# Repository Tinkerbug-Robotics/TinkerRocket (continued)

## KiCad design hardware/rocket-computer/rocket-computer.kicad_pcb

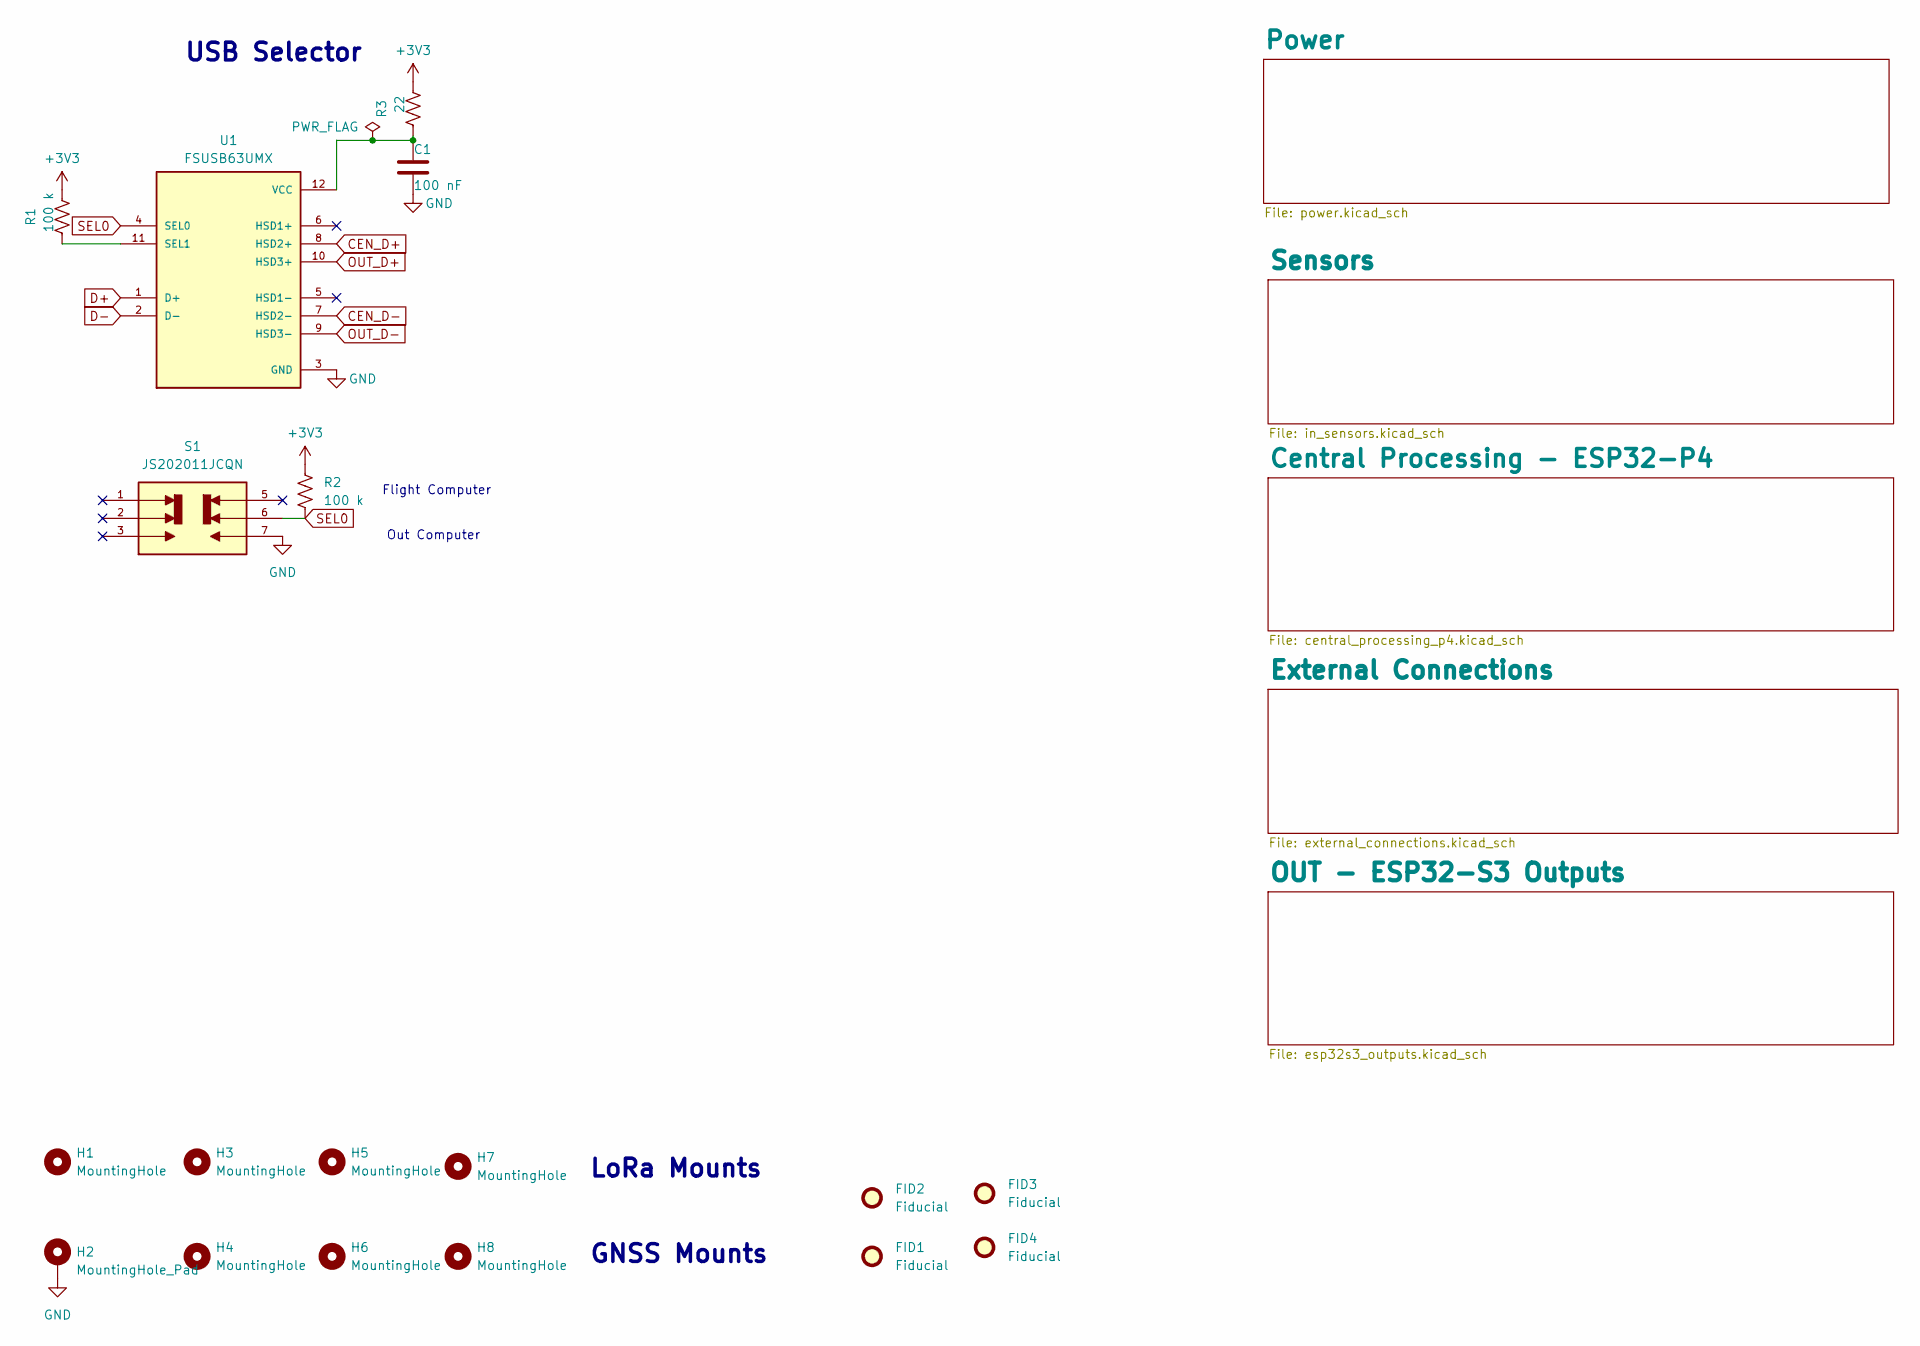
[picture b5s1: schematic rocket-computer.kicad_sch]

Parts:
C1: 100 nF; C_0402_1005Metric; MPN CL05B104KO5NNNC
FID1, FID2, FID3, FID4: Fiducial; Fiducial_0.5mm_Mask1mm
H1, H3, H4, H5, H6, H7, H8: MountingHole; MountingHole_2.2mm_M2_DIN965_Pad_TopBottom
H2: MountingHole_Pad; MountingHole_2.2mm_M2_DIN965_Pad_TopBottom
R1, R2: 100 k; R_0402_1005Metric; MPN RC0402FR-07100KL
R3: 22; R_0402_1005Metric; MPN RC0402FR-0722RL
S1: JS202011JCQN; SW_JS202011JCQN; PARTREV 11 Nov 19; DigiKey_Part_Number CKN10723CT-ND
U1: FSUSB63UMX; QFN40P180X180X55-12N; MPN FSUSB63UMX

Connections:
+3V3: R1.2, R2.2, R3.2; also elsewhere on the board
CEN_D+: U1.8 (HSD2+); also elsewhere on the board
CEN_D-: U1.7 (HSD2-); also elsewhere on the board
D+: U1.1 (D+); also elsewhere on the board
D-: U1.2 (D-); also elsewhere on the board
GND: C1.2, H2.1 (1_1), S1.7, U1.3 (GND); also elsewhere on the board
unnamed: R1.1, U1.11 (SEL1)
unnamed: C1.1, R3.1, U1.12 (VCC)
OUT_D+: U1.10 (HSD3+); also elsewhere on the board
OUT_D-: U1.9 (HSD3-); also elsewhere on the board
SEL0: R2.1, S1.6, U1.4 (SEL0)

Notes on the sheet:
GNSS Mounts
Out Computer
USB Selector
Flight Computer
LoRa Mounts

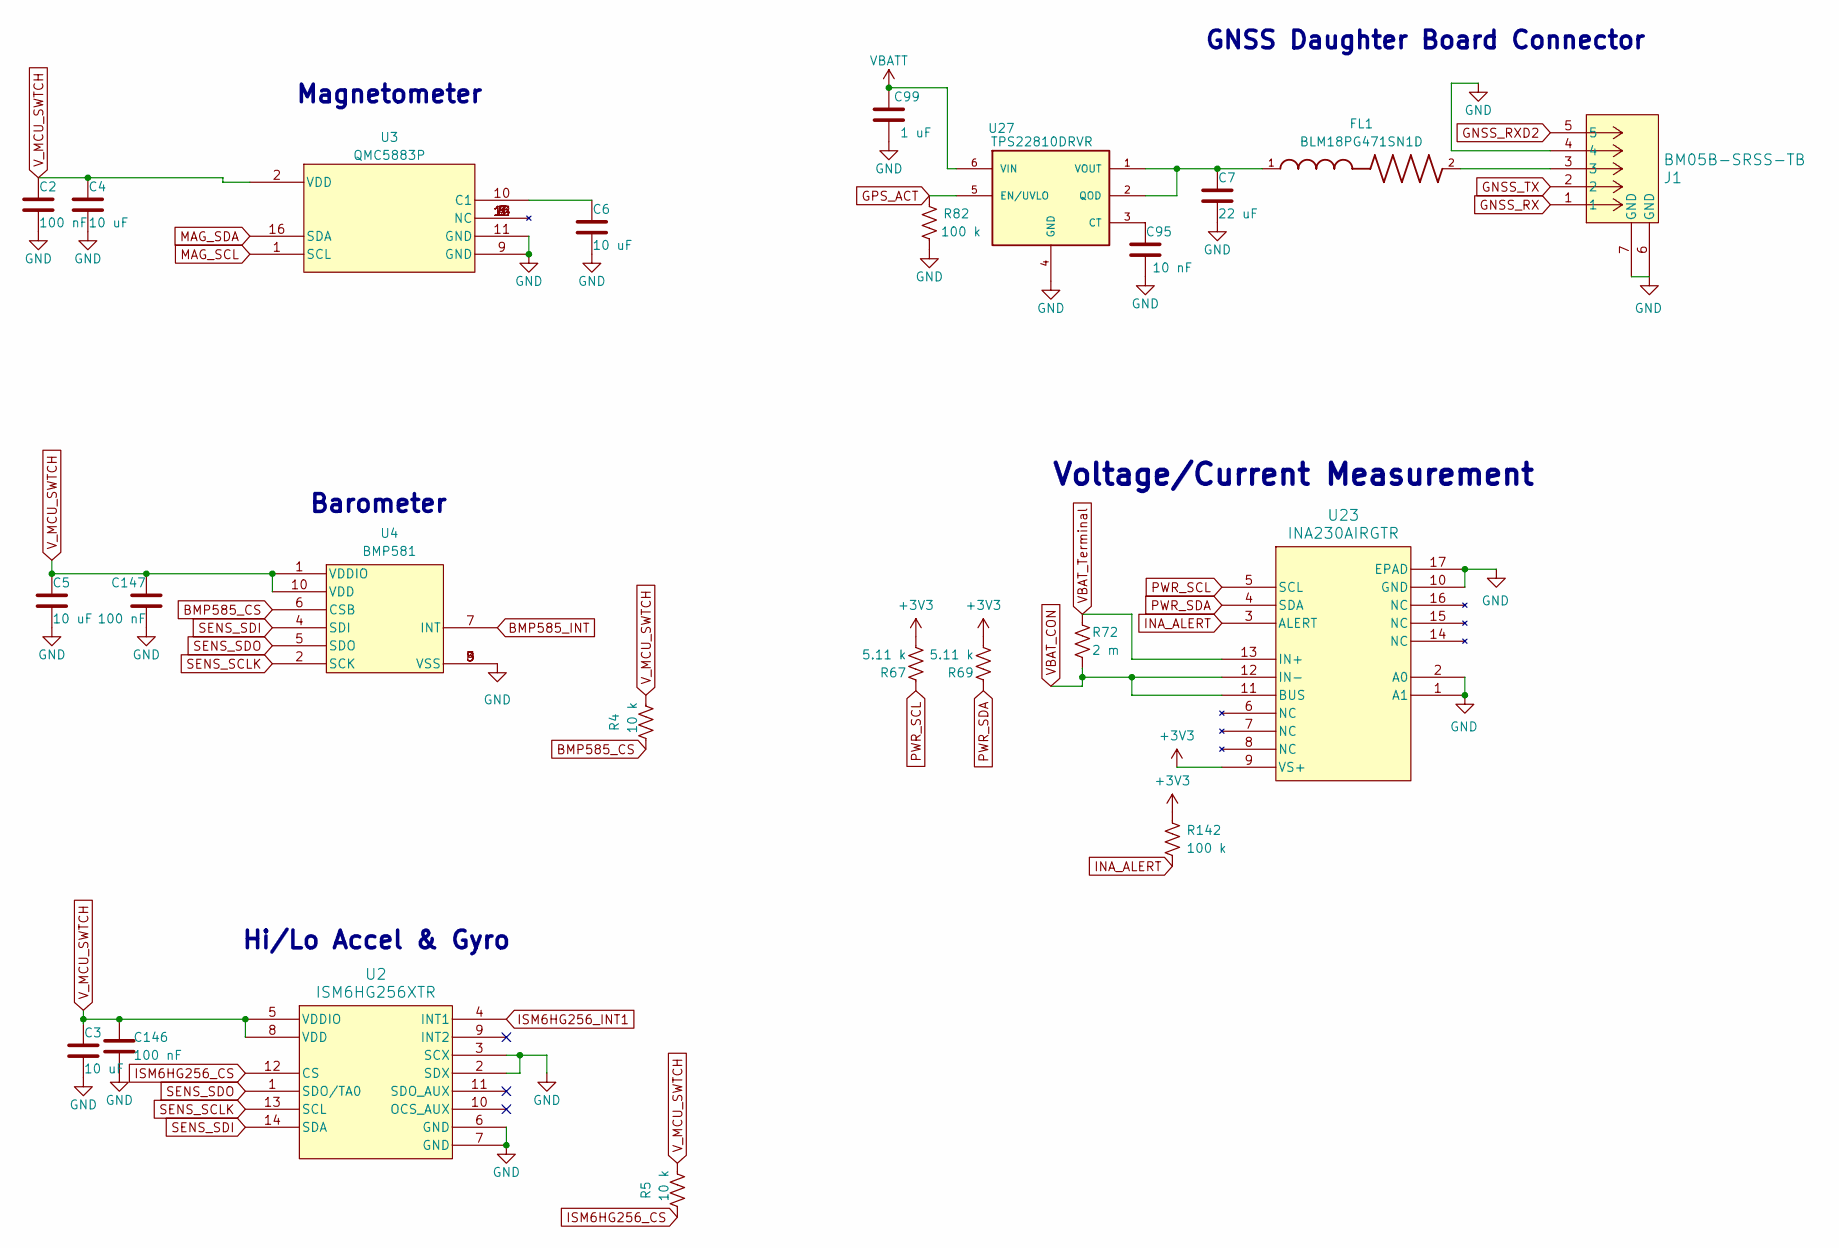
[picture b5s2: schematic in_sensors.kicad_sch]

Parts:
C2, C146, C147: 100 nF; C_0402_1005Metric; MPN CL05B104KO5NNNC
C3, C4, C5, C6: 10 uF; C_0402_1005Metric; MPN CL05A106MQ5NUNC
C7: 22 uF; C_0805_2012Metric; MPN CL21A226MOQNNNE
C95: 10 nF; C_0402_1005Metric; MPN CL05B103KB5NNNC
C99: 1 uF; C_0402_1005Metric; MPN CL05A105KO5NNNC
FL1: BLM18PG471SN1D; BEADC1608X95N; MPN BLM18PG471SN1D
J1: BM05B-SRSS-TB; CONN_BM05B-SRSS-TB_JST; MPN BM05B-SRSS-TB
R4, R5: 10 k; R_0402_1005Metric; MPN RC0402FR-0710KL
R67, R69: 5.11 k; R_0402_1005Metric; MPN RC0402FR-075K11L
R72: 2 m; R_0805_2012Metric; MPN PA0805FRF870R002L
R82, R142: 100 k; R_0402_1005Metric; MPN RC0402FR-07100KL
U2: ISM6HG256XTR; U_LGA-14L_2p5X3p0X0p83_STM; MPN ISM6HG256XTR
U3: QMC5883P; QMC5883P_LGA-16_3x3; MPN QMC5883P
U4: BMP581; BMP581_LGA-10_2x2; MPN BMP581
U23: INA230AIRGTR; RGT16_1P7X1P7; MPN INA230AIRGTR
U27: TPS22810DRVR; SON65P200X200X80-7N; MPN TPS22810DRVR

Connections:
+3V3: R67.1, R69.1, R142.1, U23.9 (VS+); also elsewhere on the board
BMP585_CS: R4.1, U4.6 (CSB); also elsewhere on the board
BMP585_INT: U4.7 (INT); also elsewhere on the board
GND: C2.2, C3.2, C4.2, C5.2, C6.2, C7.2, C95.2, C99.2, C146.2, C147.2, J1.4, J1.6 (GND), J1.7 (GND), R82.2, U2.2 (SDX), U2.3 (SCX), U2.6 (GND), U2.7 (GND), U3.9 (GND), U3.11 (GND), U4.3 (VSS), U4.8 (VSS), U4.9 (VSS), U23.1 (A1), U23.2 (A0), U23.10 (GND), U23.17 (EPAD), U27.4 (GND), U27.7 (GND); also elsewhere on the board
GNSS_RX: J1.1; also elsewhere on the board
GNSS_RXD2: J1.5; also elsewhere on the board
GNSS_TX: J1.2; also elsewhere on the board
GPS_ACT: R82.1, U27.5 (EN/UVLO); also elsewhere on the board
INA_ALERT: R142.2, U23.3 (ALERT); also elsewhere on the board
ISM6HG256_CS: R5.1, U2.12 (CS); also elsewhere on the board
ISM6HG256_INT1: U2.4 (INT1); also elsewhere on the board
MAG_SCL: U3.1 (SCL); also elsewhere on the board
MAG_SDA: U3.16 (SDA); also elsewhere on the board
unnamed: FL1.2, J1.3
unnamed: C6.1, U3.10 (C1)
unnamed: C95.1, U27.3 (CT)
unnamed: C7.1, FL1.1, U27.1 (VOUT), U27.2 (QOD)
PWR_SCL: R67.2, U23.5 (SCL); also elsewhere on the board
PWR_SDA: R69.2, U23.4 (SDA); also elsewhere on the board
SENS_SCLK: U2.13 (SCL), U4.2 (SCK); also elsewhere on the board
SENS_SDI: U2.14 (SDA), U4.4 (SDI); also elsewhere on the board
SENS_SDO: U2.1 (SDO/TA0), U4.5 (SDO); also elsewhere on the board
VBATT: C99.1, U27.6 (VIN); also elsewhere on the board
VBAT_CON: R72.1, U23.11 (BUS), U23.12 (IN-); also elsewhere on the board
VBAT_Terminal: R72.2, U23.13 (IN+); also elsewhere on the board
V_MCU_SWTCH: C2.1, C3.1, C4.1, C5.1, C146.1, C147.1, R4.2, R5.2, U2.5 (VDDIO), U2.8 (VDD), U3.2 (VDD), U4.1 (VDDIO), U4.10 (VDD); also elsewhere on the board

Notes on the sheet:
Barometer
Hi/Lo Accel & Gyro
Magnetometer
GNSS Daughter Board Connector
Voltage/Current Measurement

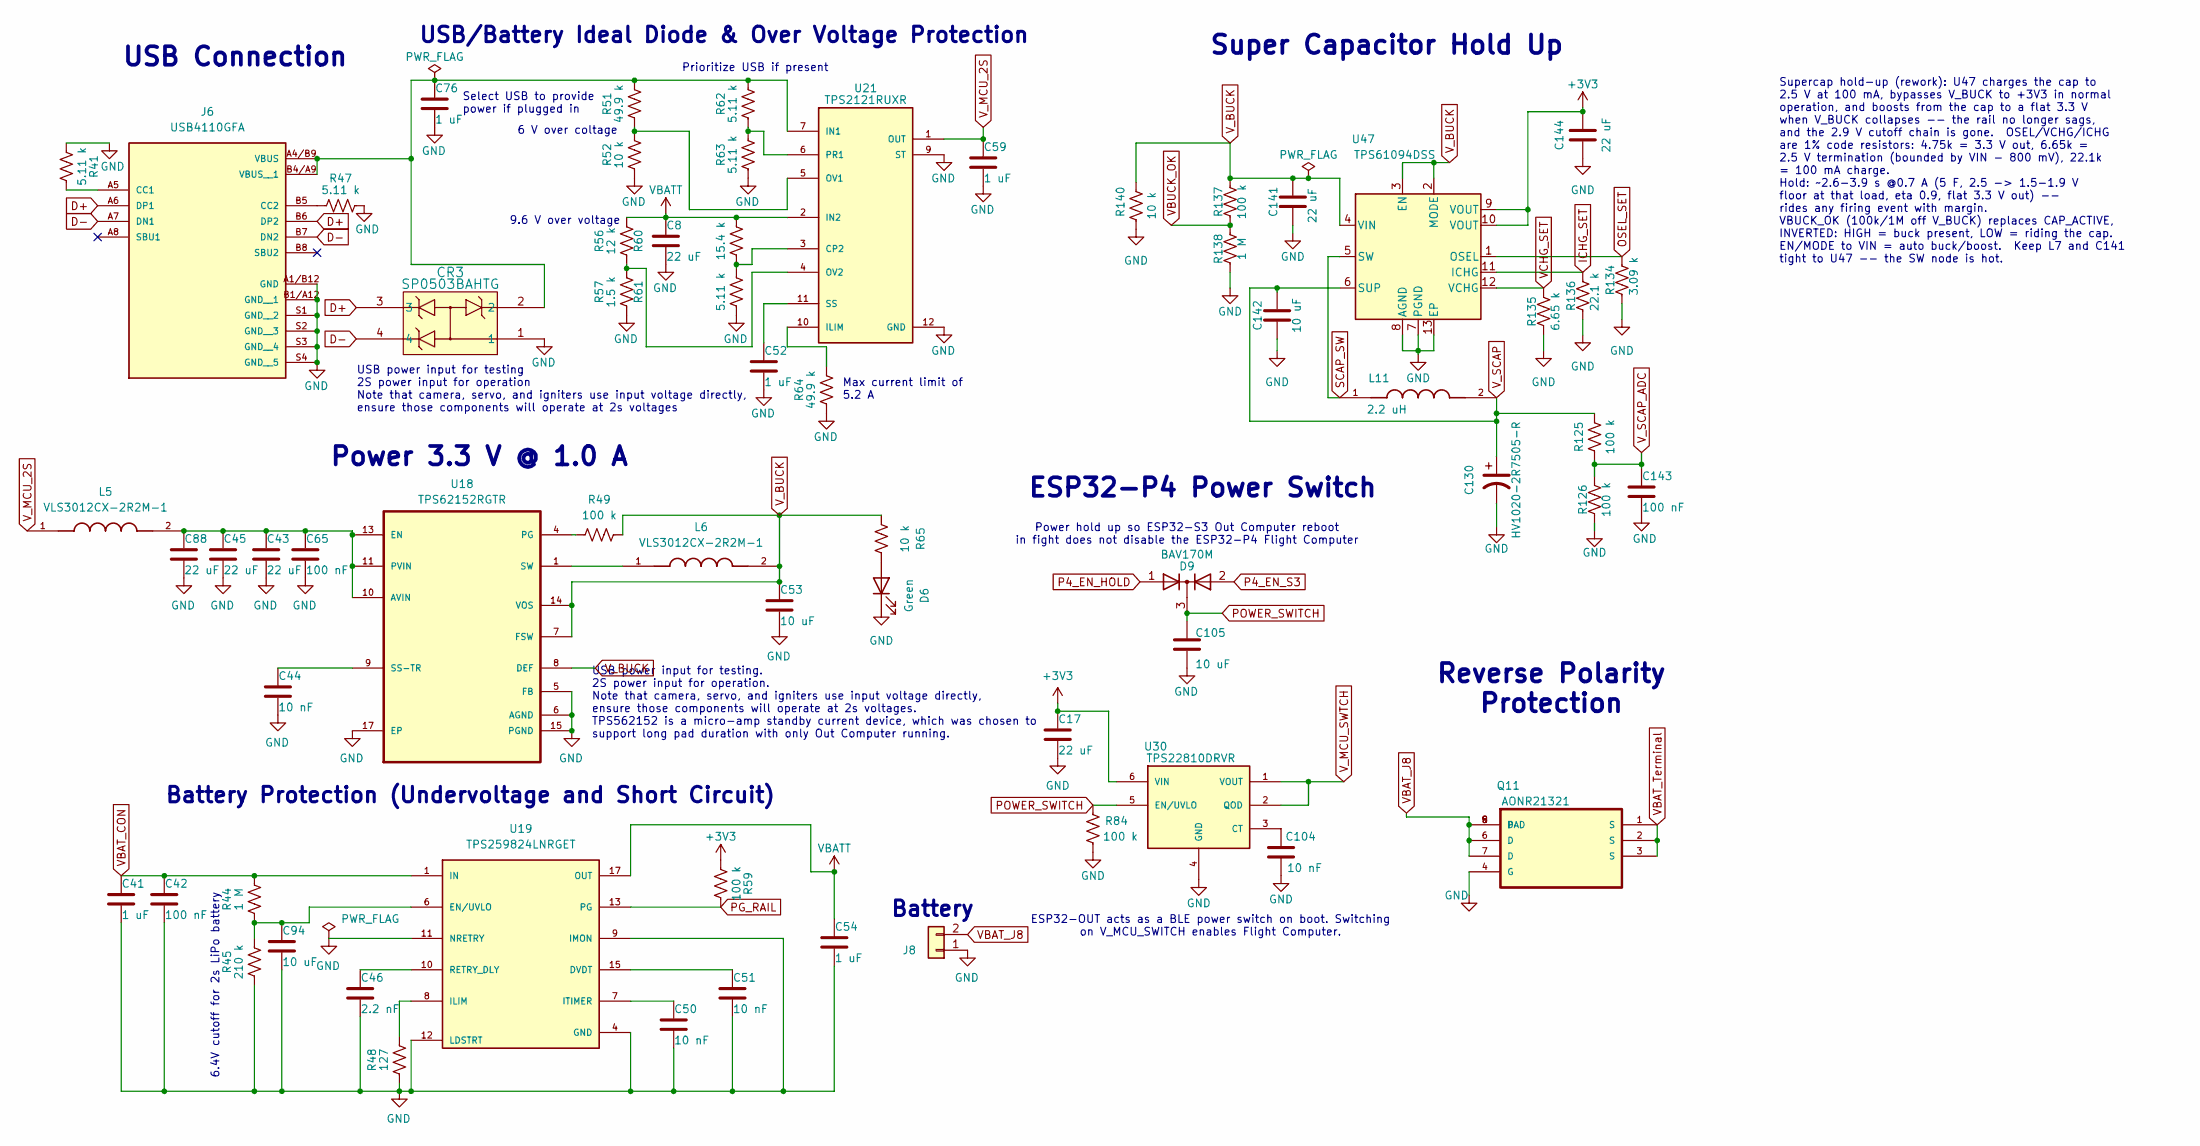
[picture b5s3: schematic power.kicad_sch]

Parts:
C8, C17, C43, C45, C88, C141, C144: 22 uF; C_0805_2012Metric; MPN CL21A226MOQNNNE
C41, C52, C54, C59, C76: 1 uF; C_0402_1005Metric; MPN CL05A105KO5NNNC
C42, C65, C143: 100 nF; C_0402_1005Metric; MPN CL05B104KO5NNNC
C44, C50, C51, C104: 10 nF; C_0402_1005Metric; MPN CL05B103KB5NNNC
C46: 2.2 nF; C_0402_1005Metric; MPN CC0402KRX7R9BB222
C53, C94, C105, C142: 10 uF; C_0402_1005Metric; MPN CL05A106MQ5NUNC
C130: HV1020-2R7505-R; CP_Radial_D10.0mm_P5.00mm; MPN HV1020-2R7505-R
CR3: SP0503BAHTG; TVS-SP05_LTF; MPN SP0503BAHTG
D6: Green; LED_0402_1005Metric; MPN XL-1005UGC
D9: BAV170M; SOT-883; MPN BAV170M,315
J6: USB4110GFA; GCT_USB4110GFA; MPN USB4110-GF-A
J8: JST_B2P-VH; JST_VH_B2P-VH_1x02_P3.96mm_Vertical; MPN B2P-VH(LF)(SN)
L5, L6: VLS3012CX-2R2M-1; IND_VLS3012CX-2R2M-1; PARTREV N/A
L11: 2.2 uH; L_XGL4020_4.0x4.0mm; MPN XGL4020-222ME
Q11: AONR21321; DFN-8-1EP_3x3mm_P0.65mm_EP1.55x2.4mm; MPN AONR21321
R41, R47, R61, R62, R63: 5.11 k; R_0402_1005Metric; MPN RC0402FR-075K11L
R44, R138: 1 M; R_0402_1005Metric; MPN RC0402FR-071ML
R45: 210 k; R_0402_1005Metric; MPN RC0402FR-07210KL
R48: 127; R_0402_1005Metric; MPN RC0402FR-07127RL
R49, R59, R84, R125, R126, R137: 100 k; R_0402_1005Metric; MPN RC0402FR-07100KL
R51, R64: 49.9 k; R_0402_1005Metric; MPN RC0402FR-0749K9L
R52, R65, R140: 10 k; R_0402_1005Metric; MPN RC0402FR-0710KL
R56: 12 k; R_0402_1005Metric; MPN RC0402FR-0712KL
R57: 1.5 k; R_0402_1005Metric; MPN RC0402FR-071K5L
R60: 15.4 k; R_0402_1005Metric; MPN RC0402FR-0715K4L
R134: 3.09 k; R_0402_1005Metric; MPN RC0402FR-073K09L
R135: 6.65 k; R_0402_1005Metric; MPN RC0402FR-076K65L
R136: 22.1 k; R_0402_1005Metric; MPN RC0402FR-0722K1L
U18: TPS62152RGTR; QFN50P300X300X100-17N; MPN TPS62152RGTR; DigiKey_Part_Number 296-43621-1-ND
U19: TPS259824LNRGET; IC_TPS259827LNRGER; Part_Rev C
U21: TPS2121RUXR; IC_TPS2121RUXR; MPN TPS2121RUXR; DigiKey_Part_Number 296-53410-1-ND
U30: TPS22810DRVR; SON65P200X200X80-7N; MPN TPS22810DRVR
U47: TPS61094DSS; WSON-12-1EP_3x2mm_P0.5mm_EP1x2.65; MPN TPS61094DSSR

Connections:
+3V3: C17.1, C144.1, R59.1, U30.6 (VIN), U47.9 (VOUT), U47.10 (VOUT); also elsewhere on the board
D+: CR3.3, J6.A6 (DP1), J6.B6 (DP2); also elsewhere on the board
D-: CR3.4, J6.A7 (DN1), J6.B7 (DN2); also elsewhere on the board
GND: C8.2, C17.2, C41.2, C42.2, C43.2, C44.2, C45.2, C46.2, C50.2, C51.2, C52.2, C53.2, C54.2, C59.2, C65.2, C76.2, C88.2, C94.2, C104.2, C105.2, C130.2, C141.2, C142.2, C143.2, C144.2, CR3.1, D6.1 (K), J6.A1/B12 (GND), J6.B1/A12 (GND__1), J6.S1 (GND__2), J6.S2 (GND__3), J6.S3 (GND__4), J6.S4 (GND__5), J8.1, Q11.4 (G), R41.1, R45.1, R47.2, R48.1, R52.1, R57.1, R61.1, R63.1, R64.1, R84.2, R126.2, R134.2, R135.2, R136.2, R138.2, R140.2, U18.5 (FB), U18.6 (AGND), U18.15 (PGND), U18.16 (PGND), U18.17 (EP), U19.4 (GND), U19.5 (GND), U19.9 (IMON), U19.11 (NRETRY), U19.12 (LDSTRT), U19.14 (GND), U19.26 (GND), U21.9 (ST), U21.12 (GND), U30.4 (GND), U30.7 (GND), U47.7 (PGND), U47.8 (AGND), U47.13 (EP); also elsewhere on the board
ICHG_SET: R136.1, U47.11 (ICHG)
unnamed: D6.2 (A), R65.2
unnamed: J6.A5 (CC1), R41.2
unnamed: J6.B5 (CC2), R47.1
unnamed: C76.1, CR3.2, J6.A4/B9 (VBUS), J6.B4/A9 (VBUS__1), R51.2, R62.2, U21.7 (IN1)
unnamed: L6.1, U18.1 (SW), U18.2 (SW), U18.3 (SW)
unnamed: C43.1, C45.1, C65.1, C88.1, L5.2, U18.10 (AVIN), U18.11 (PVIN), U18.12 (PVIN), U18.13 (EN)
unnamed: R49.1, U18.4 (PG)
unnamed: C44.1, U18.9 (SS-TR)
unnamed: C51.1, U19.15 (DVDT)
unnamed: C94.1, R44.1, R45.2, U19.6 (EN/UVLO)
unnamed: R48.2, U19.8 (ILIM)
unnamed: C50.1, U19.7 (ITIMER)
unnamed: C46.1, U19.10 (RETRY_DLY)
unnamed: R60.1, R61.2, U21.3 (CP2)
unnamed: R64.2, U21.10 (ILIM)
unnamed: R51.1, R52.2, U21.5 (OV1)
unnamed: R56.1, R57.2, U21.4 (OV2)
unnamed: R62.1, R63.2, U21.6 (PR1)
unnamed: C52.1, U21.11 (SS)
unnamed: C104.1, U30.3 (CT)
OSEL_SET: R134.1, U47.1 (OSEL)
P4_EN_HOLD: D9.1 (A); also elsewhere on the board
P4_EN_S3: D9.2 (A); also elsewhere on the board
PG_RAIL: R59.2, U19.13 (PG); also elsewhere on the board
POWER_SWITCH: C105.1, D9.3 (K), R84.1, U30.5 (EN/UVLO)
SCAP_SW: L11.1, U47.5 (SW)
VBATT: C8.1, C54.1, R56.2, R60.2, U19.17 (OUT), U19.18 (OUT), U19.19 (OUT), U19.20 (OUT), U19.21 (OUT), U19.22 (OUT), U19.23 (OUT), U19.24 (OUT), U21.2 (IN2); also elsewhere on the board
VBAT_CON: C41.1, C42.1, R44.2, U19.1 (IN), U19.2 (IN), U19.3 (IN), U19.16 (IN), U19.25 (IN); also elsewhere on the board
VBAT_J8: J8.2, Q11.5 (D), Q11.6 (D), Q11.7 (D), Q11.8 (D), Q11.9 (PAD)
VBAT_Terminal: Q11.1 (S), Q11.2 (S), Q11.3 (S); also elsewhere on the board
VBUCK_OK: R137.2, R138.1; also elsewhere on the board
VCHG_SET: R135.1, U47.12 (VCHG)
V_BUCK: C53.1, C141.1, L6.2, R49.2, R65.1, R137.1, R140.1, U18.7 (FSW), U18.8 (DEF), U18.14 (VOS), U47.2 (MODE), U47.3 (EN), U47.4 (VIN)
V_MCU_2S: C59.1, L5.1, U21.1 (OUT), U21.8 (OUT)
V_MCU_SWTCH: U30.1 (VOUT), U30.2 (QOD); also elsewhere on the board
V_SCAP: C130.1, C142.1, L11.2, R125.1, U47.6 (SUP)
V_SCAP_ADC: C143.1, R125.2, R126.1; also elsewhere on the board

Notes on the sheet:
6 V over coltage
ESP32-P4 Power Switch
USB power input for testing. 2S power input for operation. Note that camera, servo, and igniters use input voltage directly, ensure those components will operate at 2s voltages. TPS562152 is a micro-amp standby current device, which was chosen to support long pad duration with only Out Computer run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
USB/Battery Ideal Diode & Over Voltage Protection
Max current limit of 5.2 A
Reverse Polarity Protection
Power 3.3 V @ 1.0 A
Prioritize USB if present
ESP32-OUT acts as a BLE power switch on boot. Switching on V_MCU_SWITCH enables Flight Computer.
Select USB to provide power if plugged in
Power hold up so ESP32-S3 Out Computer reboot in fight does not disable the ESP32-P4 Flight Computer
9.6 V over voltage
Supercap hold-up (rework): U47 charges the cap to 2.5 V at 100 mA, bypasses V_BUCK to +3V3 in normal operation, and boosts from the cap to a flat 3.3 V when V_BUCK collapses -- the rail no longer sags, and the 2.9 V cutoff chain is gone. OSEL/VCHG/ICHG are 1% code resistors: 4.75k = 3.3 V out, 6.65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
6.4V cutoff for 2s LiPo battery
Battery Protection (Undervoltage and Short Circuit)
USB Connection
Super Capacitor Hold Up
Battery
USB power input for testing 2S power input for operation Note that camera, servo, and igniters use input voltage directly, ensure those components will operate at 2s voltages

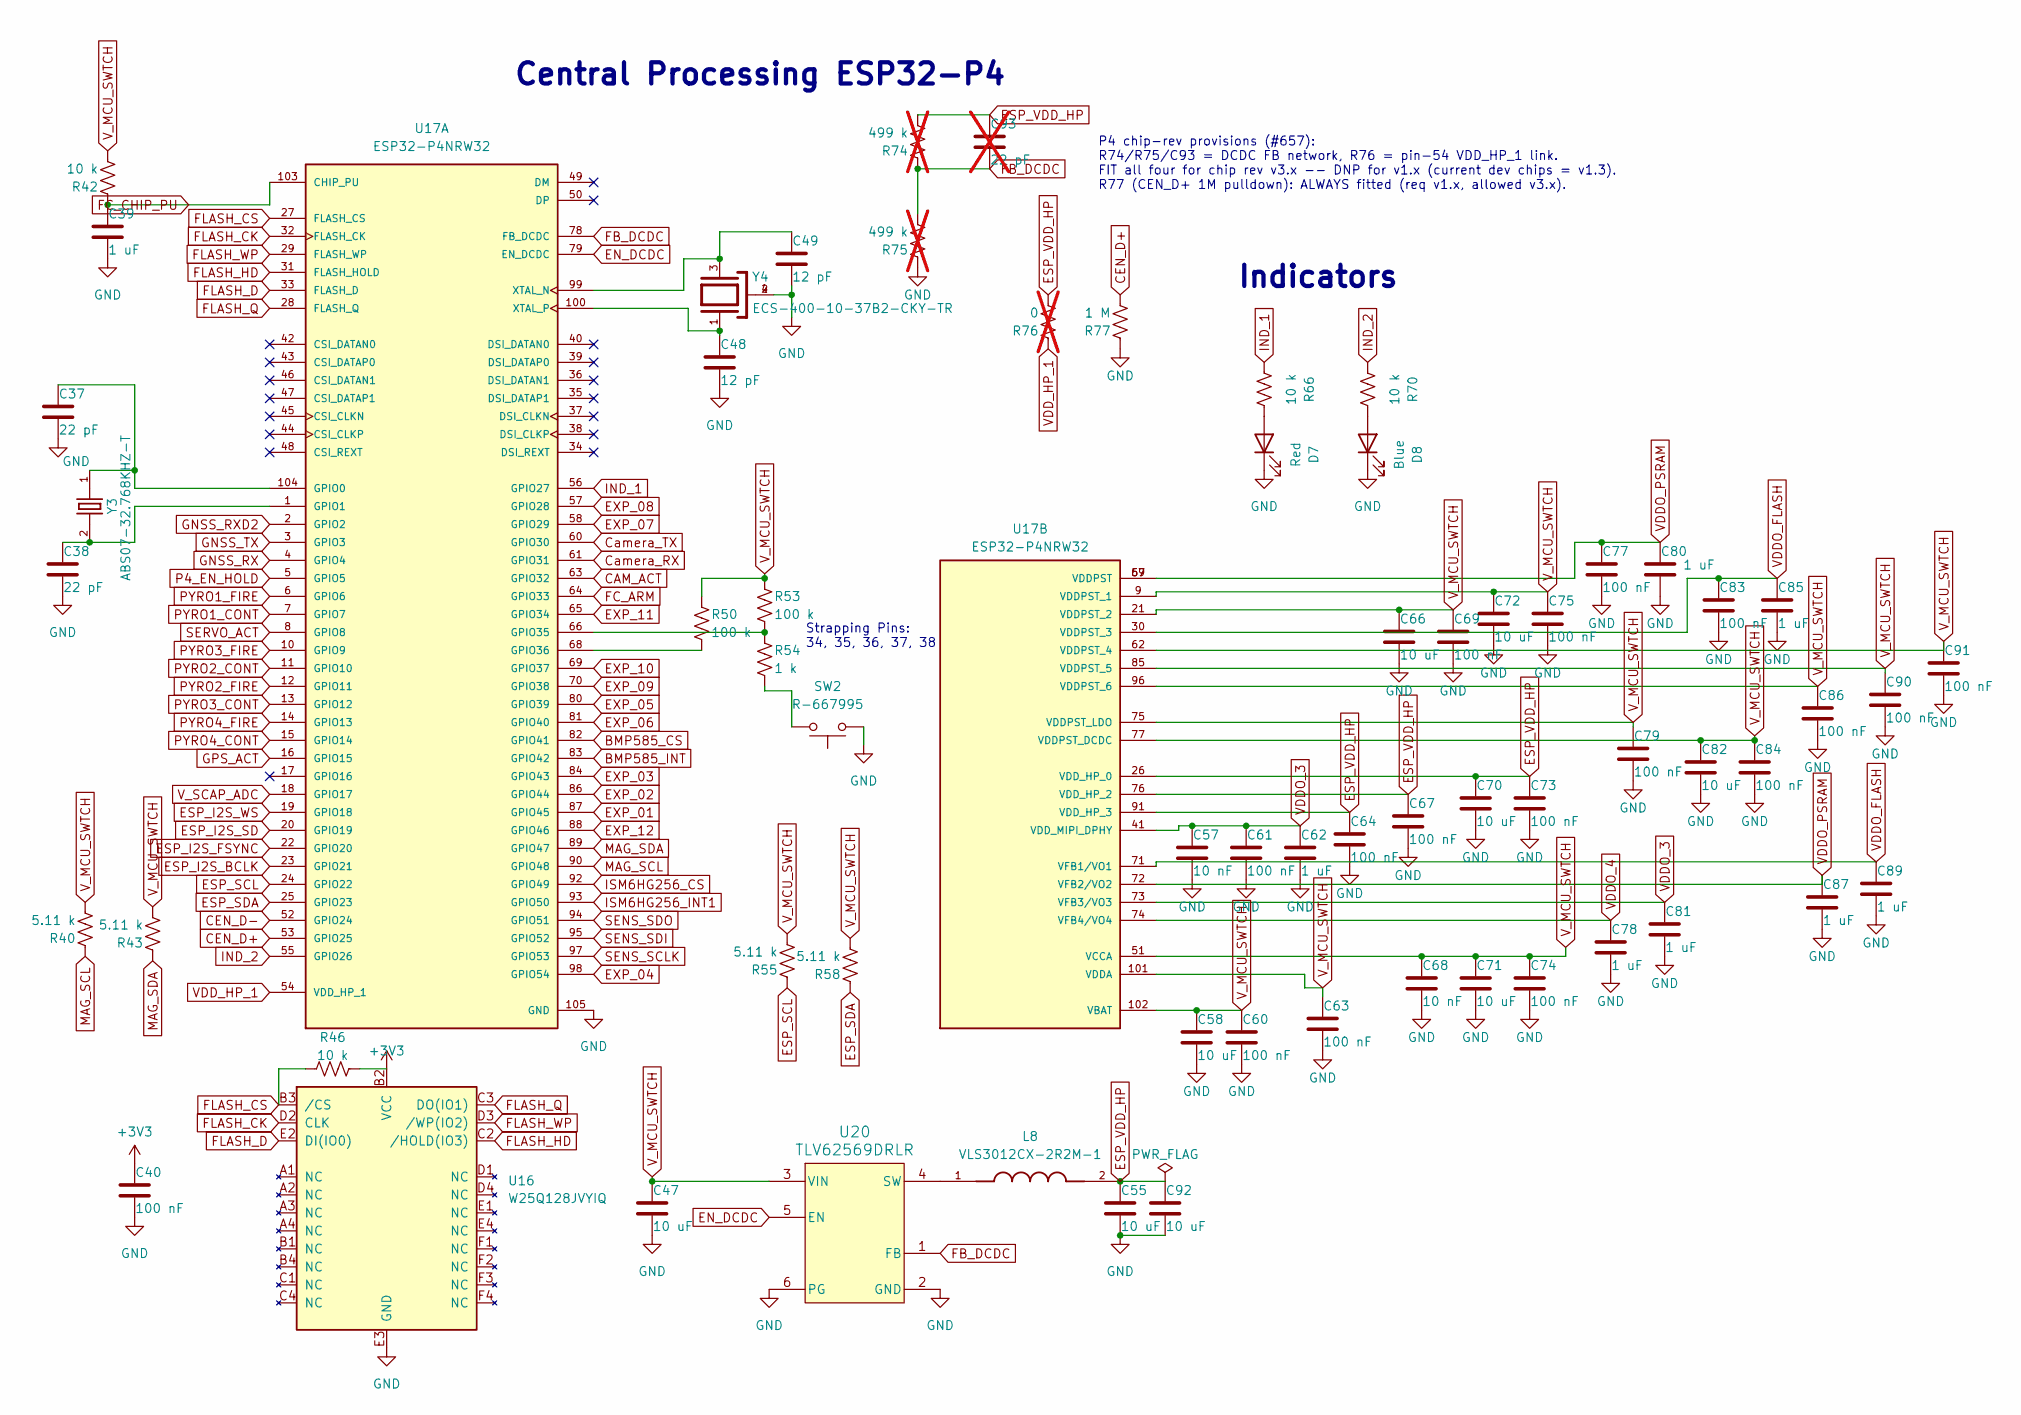
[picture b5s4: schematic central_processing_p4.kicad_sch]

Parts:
C37, C38: 22 pF; C_0402_1005Metric; MPN CL05C220JB5NNNC
C39, C62, C78, C80, C81, C85, C87, C89: 1 uF; C_0402_1005Metric; MPN CL05A105KO5NNNC
C40, C60, C61, C63, C64, C67, C69, C73, C74, C75, C77, C79, C83, C84, C86, C90, C91: 100 nF; C_0402_1005Metric; MPN CL05B104KO5NNNC
C47, C55, C58, C66, C70, C71, C72, C82, C92: 10 uF; C_0402_1005Metric; MPN CL05A106MQ5NUNC
C48, C49: 12 pF; C_0402_1005Metric; MPN CL05C120JB5NNNC
C57, C68: 10 nF; C_0402_1005Metric; MPN CL05B103KB5NNNC
C93: 22 pF; C_0402_1005Metric; MPN CL05C220JB5NNNC; not fitted
D7: Red; LED_0402_1005Metric; MPN NCD0402R1
D8: Blue; LED_0402_1005Metric; MPN APHHS1005QBC/D
L8: VLS3012CX-2R2M-1; IND_VLS3012CX-2R2M-1; PARTREV N/A
R40, R43, R55, R58: 5.11 k; R_0402_1005Metric; MPN RC0402FR-075K11L
R42, R46, R66, R70: 10 k; R_0402_1005Metric; MPN RC0402FR-0710KL
R50, R53: 100 k; R_0402_1005Metric; MPN RC0402FR-07100KL
R54: 1 k; R_0402_1005Metric; MPN RC0402FR-071KL
R74, R75: 499 k; R_0402_1005Metric; MPN RC0402FR-07499KL; not fitted
R76: 0; R_0402_1005Metric; MPN RC0402JR-070RL; not fitted
R77: 1 M; R_0402_1005Metric; MPN RC0402FR-071ML
SW2: R-667995; R-667995_MIT; MPN R-667995
U16: W25Q128JVYIQ; 24-WLCSP_Y_WIN; MPN W25Q128JVYIQ
U17: ESP32-P4NRW32; IC_ESP32-P4NRW32; PARTREV v0.4
U20: TLV62569DRLR; DRL0006A; MPN TLV62569DRLR
Y3: ABS07-32.768KHZ-T; XTAL_SC-32S_3215; MPN ABS07-32.768KHZ-T
Y4: ECS-400-10-37B2-CKY-TR; XTAL_ECS-400-10-37B2-CKY-TR; PARTREV 2021

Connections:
+3V3: C40.1, R46.2, U16.B2 (VCC); also elsewhere on the board
BMP585_CS: U17.82 (GPIO41); also elsewhere on the board
BMP585_INT: U17.83 (GPIO42); also elsewhere on the board
CAM_ACT: U17.63 (GPIO32); also elsewhere on the board
CEN_D+: R77.1, U17.53 (GPIO25); also elsewhere on the board
CEN_D-: U17.52 (GPIO24); also elsewhere on the board
Camera_RX: U17.61 (GPIO31); also elsewhere on the board
Camera_TX: U17.60 (GPIO30); also elsewhere on the board
EN_DCDC: U17.79 (EN_DCDC), U20.5 (EN)
ESP_I2S_BCLK: U17.23 (GPIO21); also elsewhere on the board
ESP_I2S_FSYNC: U17.22 (GPIO20); also elsewhere on the board
ESP_I2S_SD: U17.20 (GPIO19); also elsewhere on the board
ESP_I2S_WS: U17.19 (GPIO18); also elsewhere on the board
ESP_SCL: R55.2, U17.24 (GPIO22); also elsewhere on the board
ESP_SDA: R58.2, U17.25 (GPIO23); also elsewhere on the board
ESP_VDD_HP: C55.1, C64.1, C67.1, C70.1, C73.1, C92.1, C93.1, L8.2, R74.1, R76.1, U17.26 (VDD_HP_0), U17.76 (VDD_HP_2), U17.91 (VDD_HP_3)
EXP_01: U17.87 (GPIO45); also elsewhere on the board
EXP_02: U17.86 (GPIO44); also elsewhere on the board
EXP_03: U17.84 (GPIO43); also elsewhere on the board
EXP_04: U17.98 (GPIO54); also elsewhere on the board
EXP_05: U17.80 (GPIO39); also elsewhere on the board
EXP_06: U17.81 (GPIO40); also elsewhere on the board
EXP_07: U17.58 (GPIO29); also elsewhere on the board
EXP_08: U17.57 (GPIO28); also elsewhere on the board
EXP_09: U17.70 (GPIO38); also elsewhere on the board
EXP_10: U17.69 (GPIO37); also elsewhere on the board
EXP_11: U17.65 (GPIO34); also elsewhere on the board
EXP_12: U17.88 (GPIO46); also elsewhere on the board
FB_DCDC: C93.2, R74.2, R75.1, U17.78 (FB_DCDC), U20.1 (FB)
FC_ARM: U17.64 (GPIO33); also elsewhere on the board
FC_CHIP_PU: C39.1, R42.2, U17.103 (CHIP_PU)
FLASH_CK: U16.D2 (CLK), U17.32 (FLASH_CK)
FLASH_CS: R46.1, U16.B3 (/CS), U17.27 (FLASH_CS)
FLASH_D: U16.E2 (DI(IO0)), U17.33 (FLASH_D)
FLASH_HD: U16.C2 (/HOLD(IO3)), U17.31 (FLASH_HOLD)
FLASH_Q: U16.C3 (DO(IO1)), U17.28 (FLASH_Q)
FLASH_WP: U16.D3 (/WP(IO2)), U17.29 (FLASH_WP)
GND: C37.2, C38.2, C39.2, C40.2, C47.2, C48.2, C49.2, C55.2, C57.2, C58.2, C60.2, C61.2, C62.2, C63.2, C64.2, C66.2, C67.2, C68.2, C69.2, C70.2, C71.2, C72.2, C73.2, C74.2, C75.2, C77.2, C78.2, C79.2, C80.2, C81.2, C82.2, C83.2, C84.2, C85.2, C86.2, C87.2, C89.2, C90.2, C91.2, C92.2, D7.1 (K), D8.1 (K), R75.2, R77.2, SW2.1, U16.E3 (GND), U17.105 (GND), U20.2 (GND), U20.6 (PG), Y4.2, Y4.4; also elsewhere on the board
GNSS_RX: U17.4 (GPIO4); also elsewhere on the board
GNSS_RXD2: U17.2 (GPIO2); also elsewhere on the board
GNSS_TX: U17.3 (GPIO3); also elsewhere on the board
GPS_ACT: U17.16 (GPIO15); also elsewhere on the board
IND_1: R66.1, U17.56 (GPIO27)
IND_2: R70.1, U17.55 (GPIO26)
ISM6HG256_CS: U17.92 (GPIO49); also elsewhere on the board
ISM6HG256_INT1: U17.93 (GPIO50); also elsewhere on the board
MAG_SCL: R40.2, U17.90 (GPIO48); also elsewhere on the board
MAG_SDA: R43.2, U17.89 (GPIO47); also elsewhere on the board
unnamed: D7.2 (A), R66.2
unnamed: D8.2 (A), R70.2
unnamed: R54.1, SW2.2
unnamed: C37.1, U17.104 (GPIO0), Y3.1
unnamed: C38.1, U17.1 (GPIO1), Y3.2
unnamed: R53.1, R54.2, U17.66 (GPIO35)
unnamed: R50.1, U17.68 (GPIO36)
unnamed: C49.1, U17.99 (XTAL_N), Y4.3
unnamed: C48.1, U17.100 (XTAL_P), Y4.1
unnamed: L8.1, U20.4 (SW)
P4_EN_HOLD: U17.5 (GPIO5); also elsewhere on the board
PYRO1_CONT: U17.7 (GPIO7); also elsewhere on the board
PYRO1_FIRE: U17.6 (GPIO6); also elsewhere on the board
PYRO2_CONT: U17.11 (GPIO10); also elsewhere on the board
PYRO2_FIRE: U17.12 (GPIO11); also elsewhere on the board
PYRO3_CONT: U17.13 (GPIO12); also elsewhere on the board
PYRO3_FIRE: U17.10 (GPIO9); also elsewhere on the board
PYRO4_CONT: U17.15 (GPIO14); also elsewhere on the board
PYRO4_FIRE: U17.14 (GPIO13); also elsewhere on the board
SENS_SCLK: U17.97 (GPIO53); also elsewhere on the board
SENS_SDI: U17.95 (GPIO52); also elsewhere on the board
SENS_SDO: U17.94 (GPIO51); also elsewhere on the board
SERVO_ACT: U17.8 (GPIO8); also elsewhere on the board
VDDO_3: C57.1, C61.1, C62.1, C81.1, U17.41 (VDD_MIPI_DPHY), U17.73 (VFB3/VO3)
VDDO_4: C78.1, U17.74 (VFB4/VO4)
VDDO_FLASH: C83.1, C85.1, C89.1, U17.30 (VDDPST_3), U17.71 (VFB1/VO1)
VDDO_PSRAM: C77.1, C80.1, C87.1, U17.59 (VDDPST), U17.67 (VDDPST), U17.72 (VFB2/VO2)
VDD_HP_1: R76.2, U17.54 (VDD_HP_1)
V_MCU_SWTCH: C47.1, C58.1, C60.1, C63.1, C66.1, C68.1, C69.1, C71.1, C72.1, C74.1, C75.1, C79.1, C82.1, C84.1, C86.1, C90.1, C91.1, R40.1, R42.1, R43.1, R50.2, R53.2, R55.1, R58.1, U17.9 (VDDPST_1), U17.21 (VDDPST_2), U17.51 (VCCA), U17.62 (VDDPST_4), U17.75 (VDDPST_LDO), U17.77 (VDDPST_DCDC), U17.85 (VDDPST_5), U17.96 (VDDPST_6), U17.101 (VDDA), U17.102 (VBAT), U20.3 (VIN); also elsewhere on the board
V_SCAP_ADC: U17.18 (GPIO17); also elsewhere on the board

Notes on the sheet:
Strapping Pins: 34, 35, 36, 37, 38
P4 chip-rev provisions (#657): R74/R75/C93 = DCDC FB network, R76 = pin-54 VDD_HP_1 link. FIT all four for chip rev v3.x -- DNP for v1.x (current dev chips = v1.3). R77 (CEN_D+ 1M pulldown): ALWAYS fitted (req v1.x, allowed v3.x).
Indicators
Central Processing ESP32-P4
